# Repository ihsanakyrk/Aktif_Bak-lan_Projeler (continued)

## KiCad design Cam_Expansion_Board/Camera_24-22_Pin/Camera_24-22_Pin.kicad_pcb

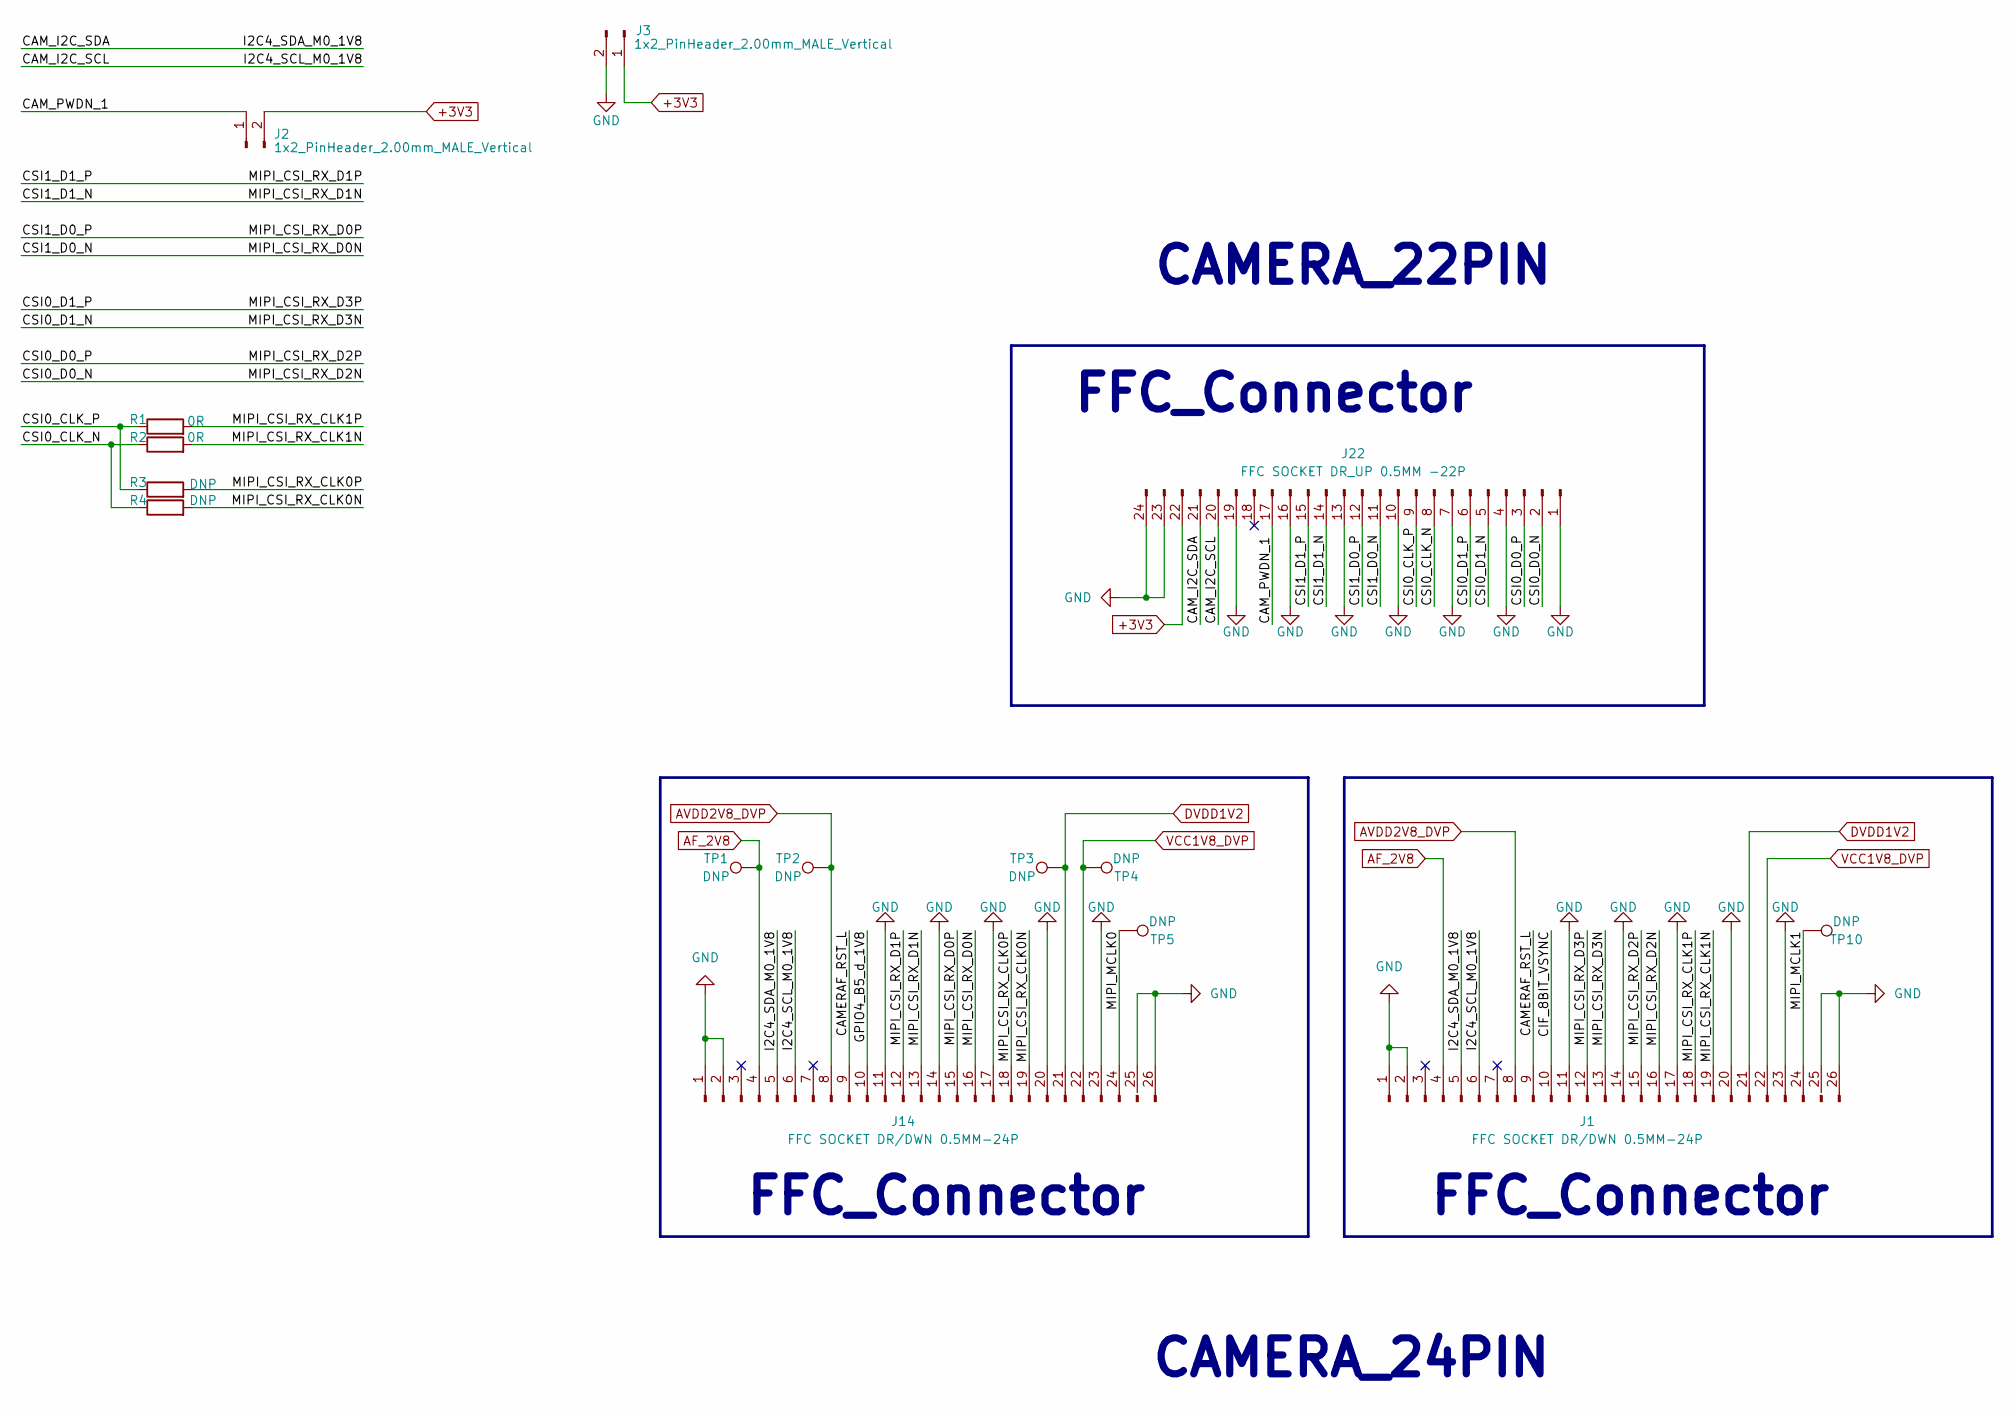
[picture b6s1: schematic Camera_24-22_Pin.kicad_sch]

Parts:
J1, J14: FFC SOCKET DR/DWN 0.5MM-24P; FFC SOCKET DRDWN 0.5MM-24P
J2, J3: 1x2_PinHeader_2.00mm_MALE_Vertical; PinHeader_1x02_P2.00mm_Vertical
J22: FFC SOCKET DR_UP 0.5MM -22P; FFC SOCKET DR_DWN 0.5MM -22P
R1, R2: 0R; R_0603_1608Metric
R3, R4: DNP; R_0603_1608Metric
TP1, TP2, TP3, TP4, TP5, TP10: DNP; Test_Point

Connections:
+3V3: J2.2, J3.1, J22.22
/CAMERAF_RST_L: J1.9, J14.9
/CAM_I2C_SCL: J1.6, J14.6, J22.20
/CAM_I2C_SDA: J1.5, J14.5, J22.21
/CAM_PWDN_1: J2.1, J22.17
/CIF_8BIT_VSYNC: J1.10
/CSI0_CLK_N: J22.8, R2.1, R4.1
/CSI0_CLK_P: J22.9, R1.1, R3.1
/CSI0_D0_N: J1.16, J22.2
/CSI0_D0_P: J1.15, J22.3
/CSI0_D1_N: J1.13, J22.5
/CSI0_D1_P: J1.12, J22.6
/CSI1_D0_N: J14.16, J22.11
/CSI1_D0_P: J14.15, J22.12
/CSI1_D1_N: J14.13, J22.14
/CSI1_D1_P: J14.12, J22.15
/GPIO4_B5_d_1V8: J14.10
/MIPI_CSI_RX_CLK0N: J14.19, R4.2
/MIPI_CSI_RX_CLK0P: J14.18, R3.2
/MIPI_CSI_RX_CLK1N: J1.19, R2.2
/MIPI_CSI_RX_CLK1P: J1.18, R1.2
/MIPI_MCLK0: J14.24, TP5.1
/MIPI_MCLK1: J1.24, TP10.1
AF_2V8: J1.4, J14.4, TP1.1
AVDD2V8_DVP: J1.8, J14.8, TP2.1
DVDD1V2: J1.21, J14.21, TP3.1
GND: J1.1, J1.2, J1.11, J1.14, J1.17, J1.20, J1.23, J1.25 (Pin_23), J1.26 (Pin_24), J3.2, J14.1, J14.2, J14.11, J14.14, J14.17, J14.20, J14.23, J14.25 (Pin_23), J14.26 (Pin_24), J22.1, J22.4, J22.7, J22.10, J22.13, J22.16, J22.19, J22.23, J22.24
VCC1V8_DVP: J1.22, J14.22, TP4.1

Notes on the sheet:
CAMERA_24PIN
FFC_Connector
CAMERA_22PIN

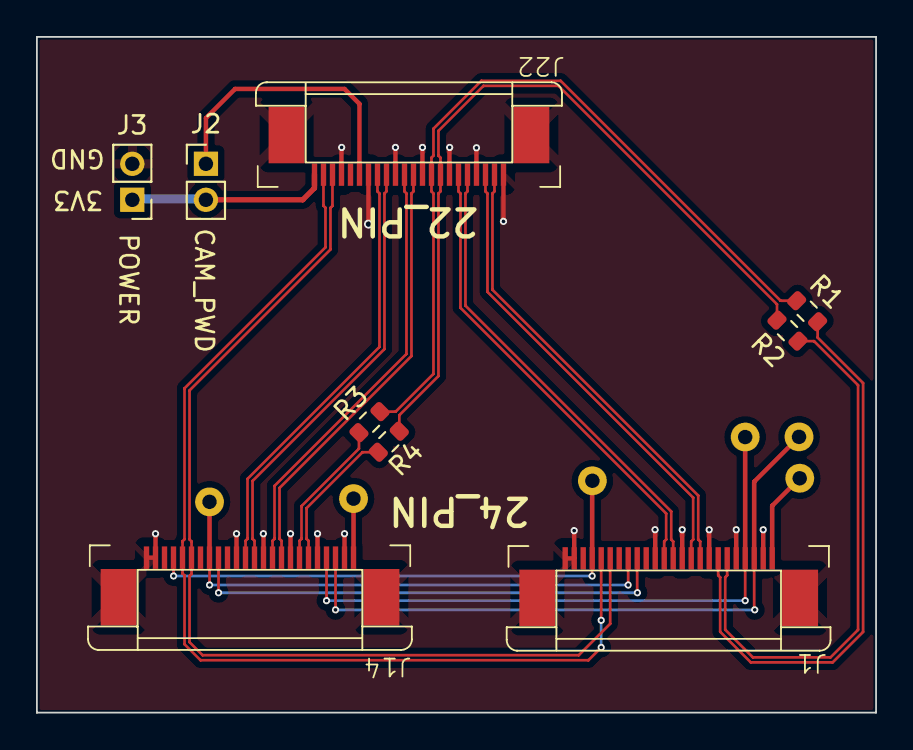
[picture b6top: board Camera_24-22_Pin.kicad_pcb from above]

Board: 2 copper layers, 46.6 x 37.5 mm, 15 parts (0 on the bottom side), 26 nets.

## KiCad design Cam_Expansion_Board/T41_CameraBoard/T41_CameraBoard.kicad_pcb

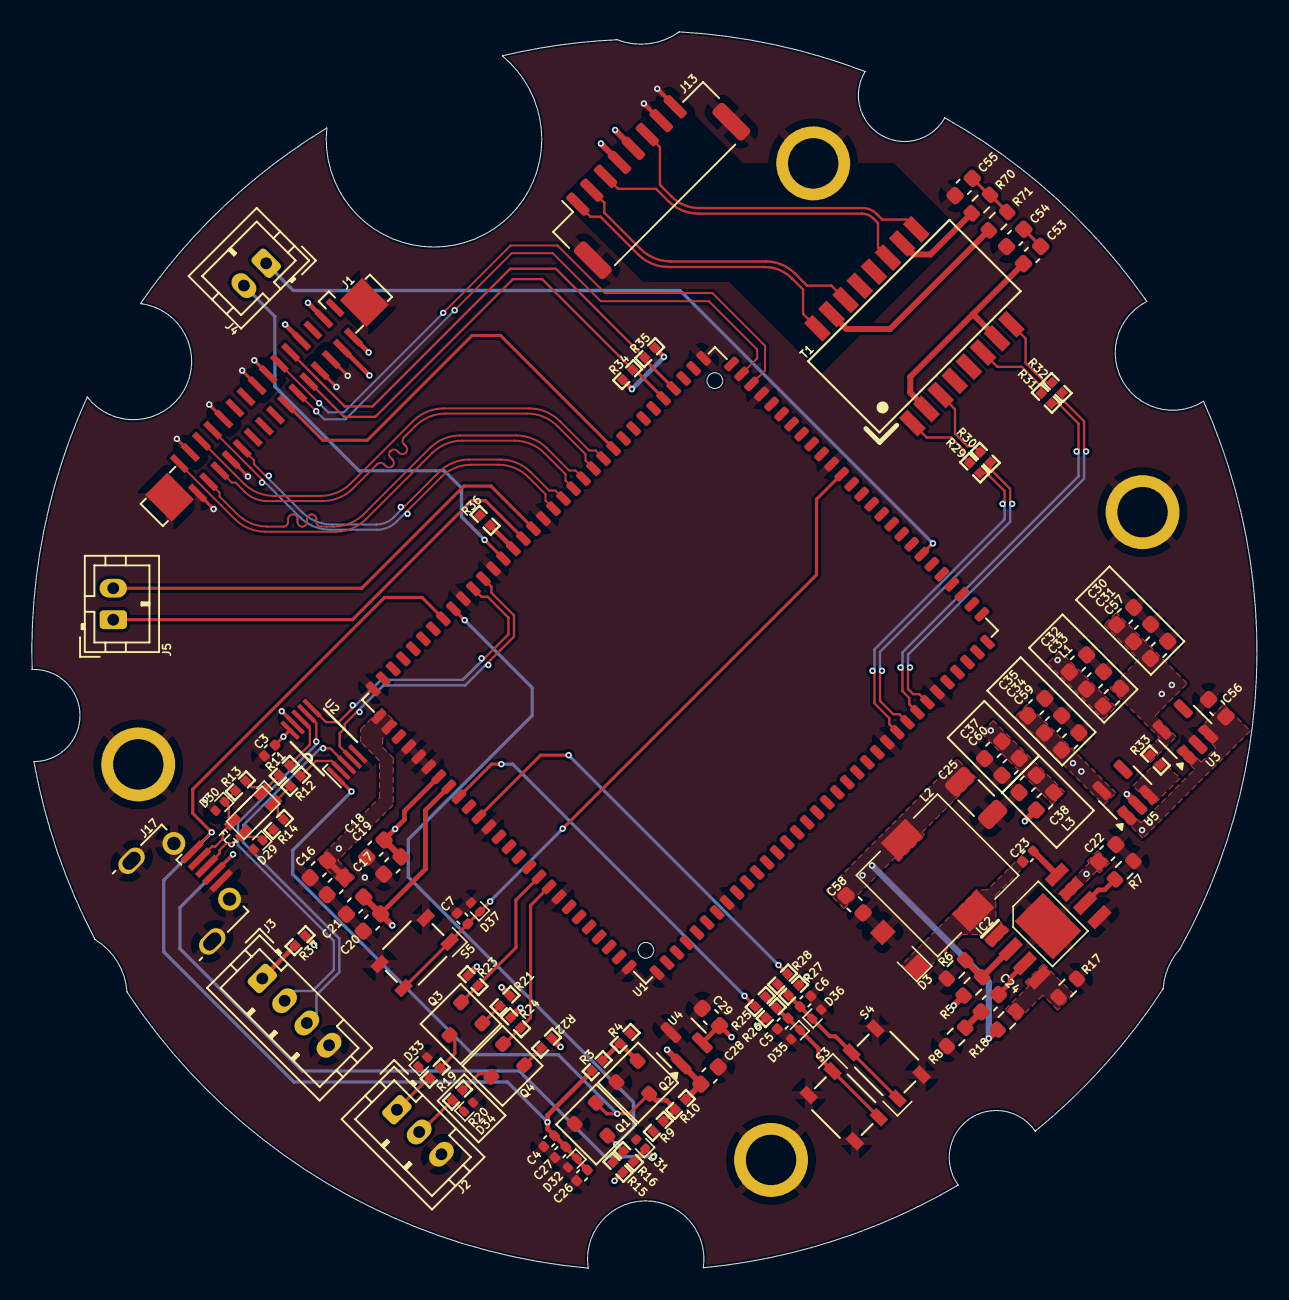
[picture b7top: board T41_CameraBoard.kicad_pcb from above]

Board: 4 copper layers, 77.9 x 78.6 mm, 111 parts (0 on the bottom side), 81 nets.

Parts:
C3, C4, C5, C6, C7, C23: 100nF; C_0402_1005Metric
C16, C18, C20: 10uF/X5R/10V; C_0603_1608Metric
C17, C19, C21: 100nF/X5R/10V; C_0603_1608Metric
C22: 10uF; C_0603_1608Metric
C24: 150pF; C_0603_1608Metric
C25: 22uF/6.3V; C_1206_3216Metric
C26: 10uF/X5R/10V; C_0402_1005Metric
C27: 0.1uF; C_0402_1005Metric
C28, C29, C30, C31, C33, C34, C35, C37, C38: 0.1uF; C_0603_1608Metric
C32: 1uF; C_0603_1608Metric
C53, C54: 0.01uF; C_0603_1608Metric
C55: 1000pF; C_0603_1608Metric
C56, C57, C58, C59, C60: 4.7uF; C_0603_1608Metric
D3: SS34C-MD; SS34FA
D29, D30: ESD5341N
D31, D32, D33, D34, D35, D36, D37: ESD5451N; ESD5341N
FL3: DNP; DLW31SH222SQ2L
H1, H2, H3, H4: DNP; T41_Mounting_Hole
IC2: MP1584EN-LF-Z; MP1584N
J1: AFC11-S30ICA-00
J2: DNP; JST_PH_B3B-PH-K_1x03_P2.00mm_Vertical
J3: DNP; JST_PH_B4B-PH-K_1x04_P2.00mm_Vertical
J4, J5: DNP; JST_PH_B2B-PH-K_1x02_P2.00mm_Vertical
J13: JST_1x8-1MP_P1.25mm_Vertical; JST_1x8_1MP_P1.25mm_Vertical
J17: MICRO XNJ ZB; Micro-B SMD
L1, L3: BLM18PG181SN1; L_0603_1608Metric
L2: SRI0704-100M
Q1, Q2, Q3, Q4: BSS138; SOT-23
R3, R4, R10, R15, R23, R24, R33, R34, R35: 10K; R0402
R5, R7, R8: 100K; R_0603_1608Metric
R6: 24.9K; R_0603_1608Metric
R9, R26, R27: 100K; R0402
R11, R12, R13, R14: 2.2R; R0402
R16, R19, R20: 100R; R0402
R17: 40.2K; R_0603_1608Metric
R18: 210K; R_0603_1608Metric
R21, R22, R25, R28: 1K; R0402
R29, R30, R31, R32, R37: 0R; R0402
R36: DNP; R0402
R70, R71: 75R; R_0603_1608Metric
S3, S4, S5: SKRPANE010
T1: H1102NL
U1: DNP; T41
U2: FSUSB30MUX; SOP50P490X110-10N
U3, U5: rt9013-28gb; SOT-23-5
U4: TLV76033DBZT; SOT-23

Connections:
1V8: C20.2, C21.2, L3.1, R15.2, R26.2, R27.2, R34.1, R35.1, U1.8
3V3: C18.2, C19.2, R23.1, R24.1, U1.7
5V_LAN: C25.1, C56.1, C58.1, L2.2, R18.2, R37.1, U3.1 (IN), U3.3 (EN), U5.1 (IN)
/AGND: R36.1, U1.106
/BOOTSEL0: C7.2 (-), D37.1, S5.1, S5.2, U1.75
/BOOT_MODE: Q1.1 (G), Q2.3 (D), R9.1, R10.1, U2.1 (S)
/HPOUT: J4.2, U1.107
/I2C0_MIPI_DVP_SCK: J1.10, R34.2, U1.91
/I2C0_MIPI_DVP_SDA: J1.9, R35.2, U1.90
/MICNL: J5.1, U1.105
/MICPL: J5.2, U1.104
/MIPI_DVP_PWDN_PA19: J1.12, U1.85
/MIPI_DVP_RESET: J1.11, U1.84
/MIPI_MCLK_PA15/DVP_MCLK_PA15: J1.14, U1.96
/MIPI_RX_2LANE_CLKN0: J1.26, U1.98
/MIPI_RX_2LANE_CLKP0: J1.25, U1.97
/MIPI_RX_2LANE_DN0: J1.29, U1.100
/MIPI_RX_2LANE_DN1: J1.23, U1.102
/MIPI_RX_2LANE_DP0: J1.28, U1.99
/MIPI_RX_2LANE_DP1: J1.22, U1.101
/OTG_ID: D31.1, J17.4 (ID), R16.2
/PPRST_N: R25.2, U1.9
/RX_N1: R32.1, U1.54
/RX_P0+: R31.2, T1.6 (RD+)
/RX_P0-: R32.2, T1.8 (RD-)
/RX_P1: R31.1, U1.53
/SPEAK_EN: J4.1, U1.67
/TX_N0: R30.1, U1.52
/TX_P0: R29.1, U1.51
/TX_P0+: R29.2, T1.1 (TD+)
/TX_P0-: R30.2, T1.3 (TD-)
/UART1-RXD: Q3.3 (D), R19.2
/UART1-TXD: Q4.3 (D), R20.2
/UART1_RXD: Q3.2 (S), R23.2, U1.17
/UART1_TXD: Q4.2 (S), R24.2, U1.18
/USB0ID: Q1.3 (D), R15.1, R16.1, U1.112
/USB-OTG-DN: FL3.1, R11.2, R13.1
/USB-OTG-DP: FL3.4, R12.2, R14.1
/USB_DN: D30.1, FL3.2, J17.2 (DM), R13.2
/USB_DN0: U1.110, U2.6 (D-)
/USB_DP: D29.1, FL3.3, J17.3 (DP), R14.2
/USB_DP0: U1.109, U2.4 (D+)
/USB_HOST_DN: J3.2, U2.7 (HSD2-)
/USB_HOST_DP: J3.3, U2.3 (HSD2+)
/USB_OTG_DN: R11.1, U2.8 (HSD1-)
/USB_OTG_DP: R12.1, U2.2 (HSD1+)
/WKUP: R28.2, U1.11
AF_2V8: C32.2, C33.2, J1.2, L1.2
AVDD2V8_DVP: C30.2, C31.2, C57.1, J1.7, L1.1, R33.2, U3.5 (OUT)
DVDD1V2: C34.2, C35.2, C59.1, J1.3, U5.5 (OUT)
GND: C3.1 (+), C4.1 (+), C5.1 (+), C6.1 (+), C7.1 (+), C16.1, C17.1, C18.1, C19.1, C20.1, C21.1, C22.1, C25.2, C26.1, C27.1, C28.1, C29.1, C30.1, C31.1, C32.1, C33.1, C34.1, C35.1, C37.1, C38.1, C54.2, C55.2, C56.2, C57.2, C58.2, C59.2, C60.2, D3.2, D29.2, D30.2, D31.2, D32.2, D33.2, D34.2, D35.2, D36.2, D37.2, H1.1 (GND), H2.1 (GND), H3.1 (GND), H4.1 (GND), IC2.5 (GND), IC2.9 (EP), J1.6, J1.8, J1.13, J1.15, J1.21, J1.24, J1.27, J1.30, J1.31, J1.32, J2.3, J3.4, J13.7, J13.8, J13.9, J13.10, J17.5 (GND), J17.6 (Shield), Q1.2 (S), Q2.2 (S), R4.1, R6.2, R7.2, R8.2, R9.2, R17.2, R36.2, S3.3, S3.4, S4.3, S4.4, S5.3, S5.4, U1.4, U1.5, U1.6, U1.12, U1.19, U1.26, U1.27, U1.34, U1.50, U1.55, U1.76, U1.83, U1.87, U1.103, U1.108, U1.111, U1.120, U2.5 (GND), U2.9 (/OE), U3.2 (GND), U4.3 (GND), U5.2 (GND)
unnamed: C5.2 (-), D35.1, R25.1, R26.1, S3.1, S3.2
unnamed: C6.2 (-), D36.1, R27.1, R28.1, S4.1, S4.2
unnamed: C24.1, R8.1
unnamed: C53.2, C54.1
unnamed: C55.1, R70.1, R71.1
unnamed: C23.2, IC2.8 (BST)
unnamed: C24.2, IC2.3 (COMP)
unnamed: IC2.2 (EN), R5.2, R6.1
unnamed: IC2.4 (FB), R17.1, R18.1
unnamed: IC2.6 (FREQ), R7.1
unnamed: C23.1, D3.1, IC2.1 (SW), L2.1
unnamed: D33.1, J2.1, R19.1
unnamed: D34.1, J2.2, R20.1
unnamed: J3.1, R37.2
unnamed: Q2.1 (G), R3.1, R4.2
unnamed: Q3.1 (G), R21.2
unnamed: Q4.1 (G), R22.2
unnamed: C53.1, T1.2 (CT1), T1.7 (CT2)
unnamed: R70.2, T1.10 (CT3)
unnamed: R71.2, T1.15 (CT4)
unnamed: R33.1, U5.3 (EN)
RX0_N: J13.6, T1.9 (RX-)
RX0_P: J13.3, T1.11 (RX+)
TRD0_N: J13.2, T1.14 (TX-)
TRD0_P: J13.1, T1.16 (TX+)
USB_VBUS: C4.2 (-), C26.2, C27.2, D32.1, J17.1 (VBUS), R3.2, U1.113
VCC1V8_DVP: C37.2, C38.2, C60.1, J1.4, L3.2
VCC_3V3: C3.2 (-), C28.2, R10.2, U2.10 (VCC), U4.1 (OUT)
VCC_5V: C16.2, C17.2, R21.1, R22.1, U1.1, U1.2
VIN: C22.2, C29.2, IC2.7 (VIN), J13.4, J13.5, R5.1, U4.2 (IN)

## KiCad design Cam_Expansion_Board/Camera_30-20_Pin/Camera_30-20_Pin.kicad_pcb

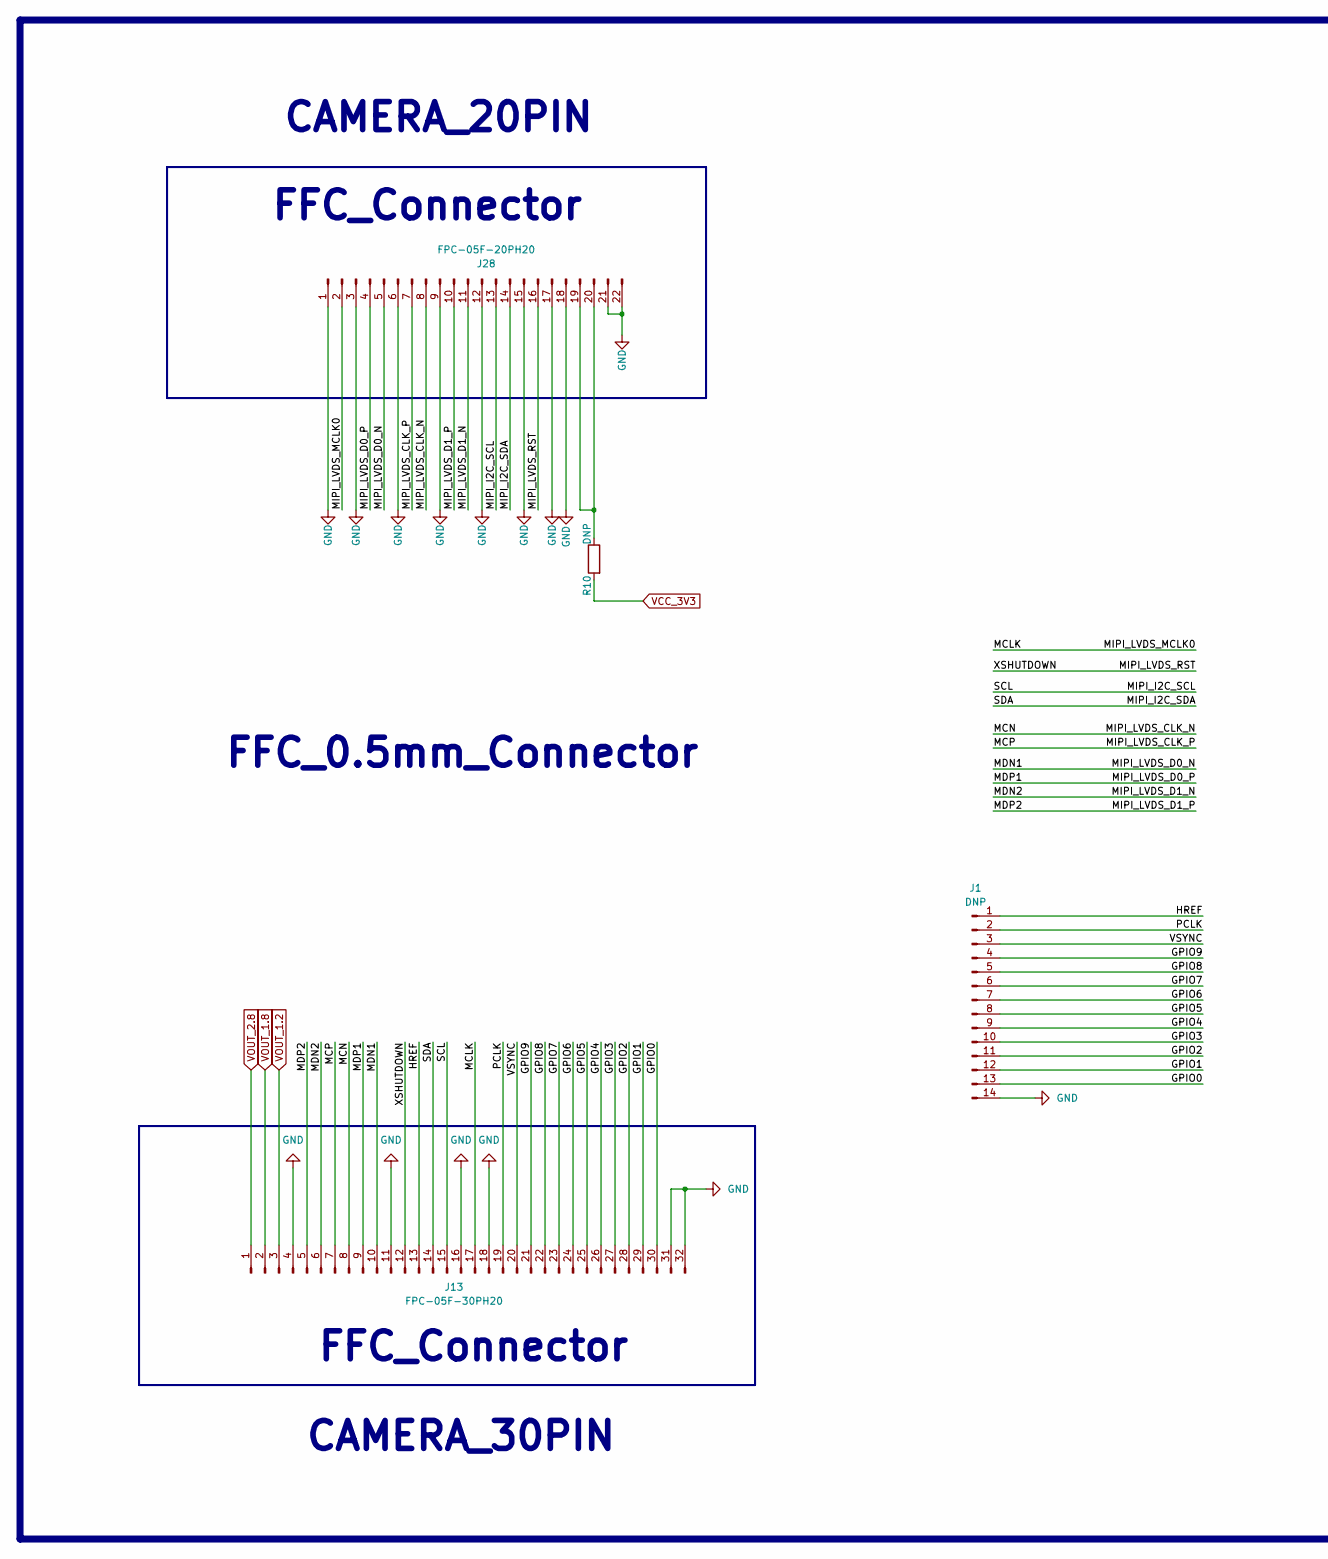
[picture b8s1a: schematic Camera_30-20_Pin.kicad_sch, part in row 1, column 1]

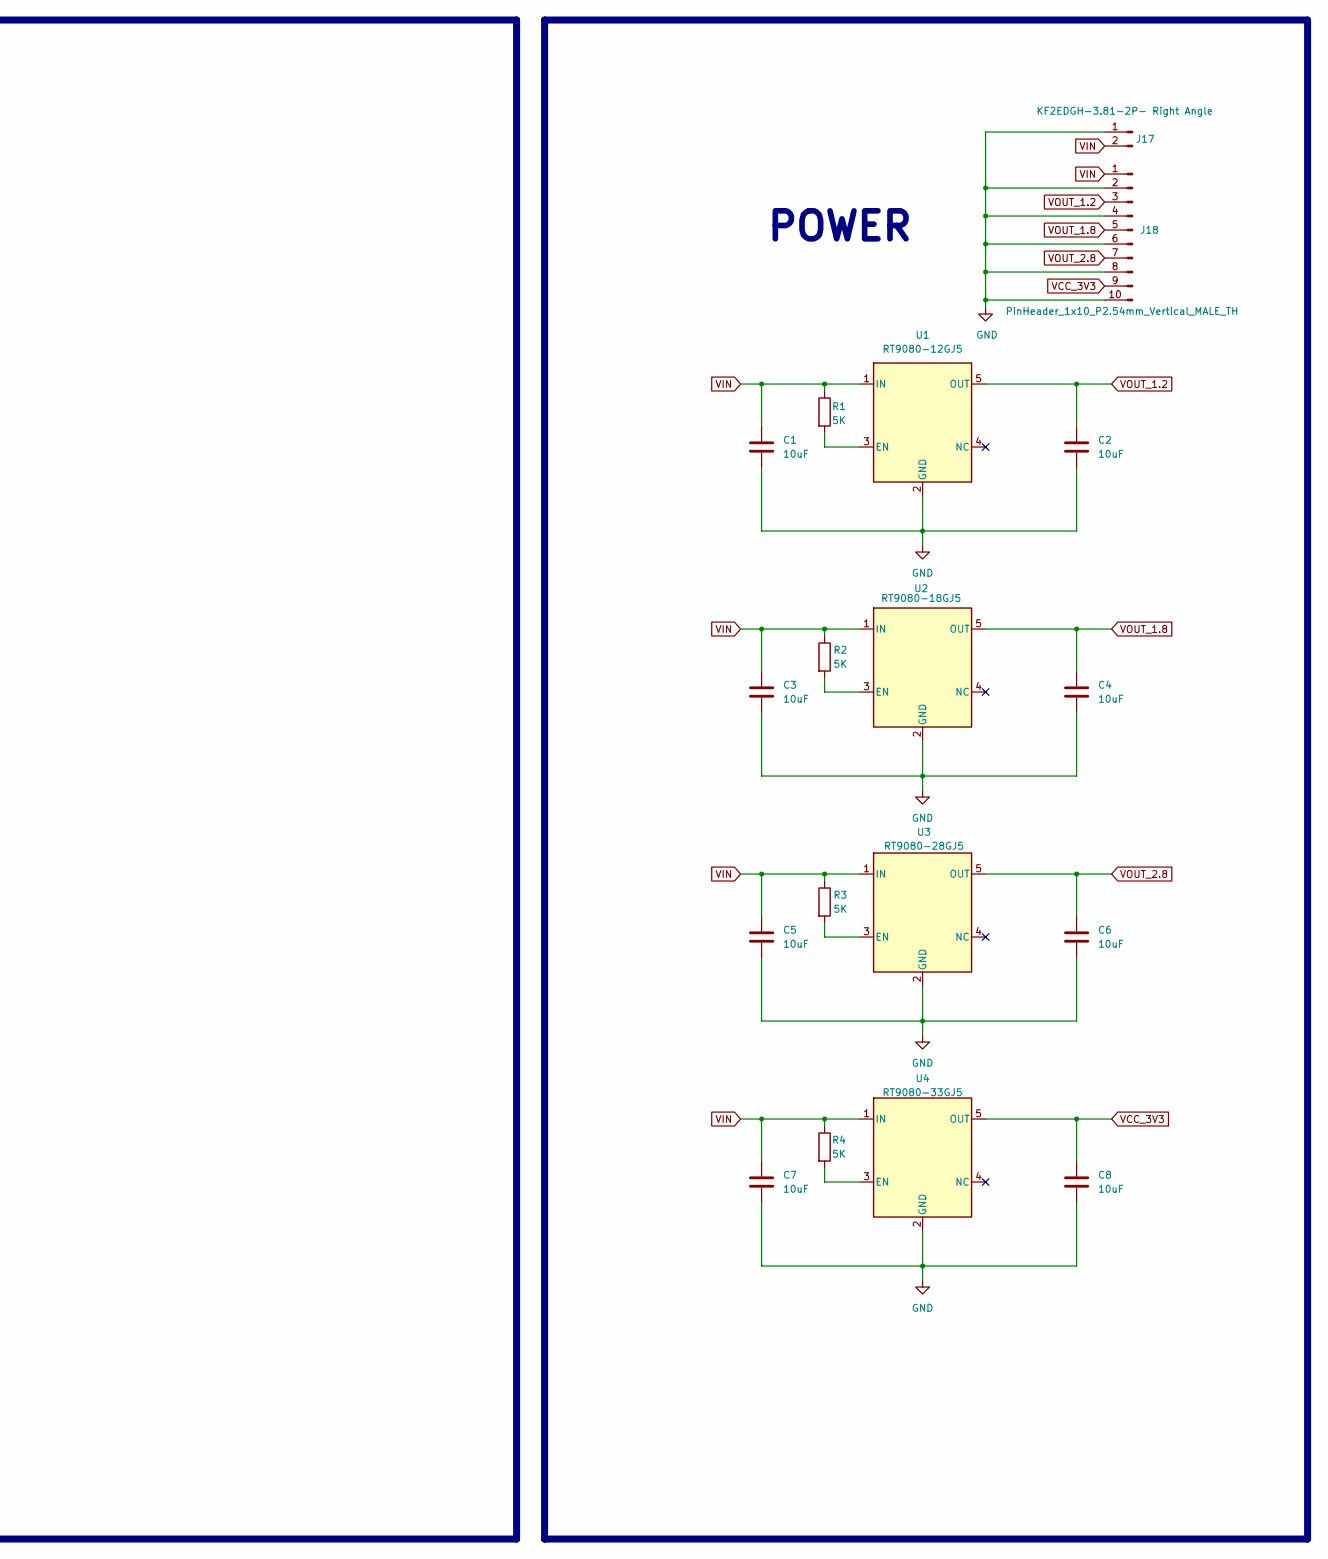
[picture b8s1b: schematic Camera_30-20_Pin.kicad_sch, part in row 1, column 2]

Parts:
C1, C2, C3, C4, C5, C6, C7, C8: 10uF; C_0805_2012Metric
J1: DNP; PinHeader_2x07_P2.00mm_Vertical
J13: FPC-05F-30PH20; FFC SOCKET DR_DWN 0.5MM-30P
J17: KF2EDGH-3.81-2P- Right Angle; KF2EDGH-3.81-2P
J18: PinHeader_1x10_P2.54mm_Vertical_MALE_TH; PinHeader_1x10_P2.54mm_Vertical
J28: FPC-05F-20PH20; FFC SOCKET DR_DWN 0.5MM -20P
R1, R2, R3, R4: 5K; R_0603_1608Metric
R10: DNP; R_0603_1608Metric
U1: RT9080-12GJ5; SOT-23-5
U2: RT9080-18GJ5; SOT-23-5
U3: RT9080-28GJ5; SOT-23-5
U4: RT9080-33GJ5; SOT-23-5

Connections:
/GPIO0: J1.13, J13.30
/GPIO1: J1.12, J13.29
/GPIO2: J1.11, J13.28
/GPIO3: J1.10, J13.27
/GPIO4: J1.9, J13.26
/GPIO5: J1.8, J13.25
/GPIO6: J1.7, J13.24
/GPIO7: J1.6, J13.23
/GPIO8: J1.5, J13.22
/GPIO9: J1.4, J13.21
/HREF: J1.1, J13.13
/MCLK: J13.17, J28.2
/MCN: J13.8, J28.8
/MCP: J13.7, J28.7
/MDN1: J13.10, J28.5
/MDN2: J13.6, J28.11
/MDP1: J13.9, J28.4
/MDP2: J13.5, J28.10
/MIPI_I2C_SCL: J13.15, J28.13
/MIPI_I2C_SDA: J13.14, J28.14
/MIPI_LVDS_RST: J13.12, J28.16
/PCLK: J1.2, J13.19
/VSYNC: J1.3, J13.20
GND: C1.2, C2.2, C3.2, C4.2, C5.2, C6.2, C7.2, C8.2, J1.14 (Pin_13), J13.4, J13.11, J13.16, J13.18, J13.31 (Pin_29), J13.32 (Pin_30), J17.1, J18.2, J18.4, J18.6, J18.8, J18.10, J28.1, J28.3, J28.6, J28.9, J28.12, J28.15, J28.17, J28.18, J28.21, J28.22, U1.2 (GND), U2.2 (GND), U3.2 (GND), U4.2 (GND)
unnamed: J28.19, J28.20, R10.1
unnamed: R1.2, U1.3 (EN)
unnamed: R2.2, U2.3 (EN)
unnamed: R3.2, U3.3 (EN)
unnamed: R4.2, U4.3 (EN)
VCC_3V3: C8.1, J18.9, R10.2, U4.5 (OUT)
VIN: C1.1, C3.1, C5.1, C7.1, J17.2, J18.1, R1.1, R2.1, R3.1, R4.1, U1.1 (IN), U2.1 (IN), U3.1 (IN), U4.1 (IN)
VOUT_1.2: C2.1, J13.3, J18.3, U1.5 (OUT)
VOUT_1.8: C4.1, J13.2, J18.5, U2.5 (OUT)
VOUT_2.8: C6.1, J13.1, J18.7, U3.5 (OUT)

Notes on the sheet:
CAMERA_20PIN
CAMERA_30PIN
FFC_0.5mm_Connector
FFC_Connector
POWER

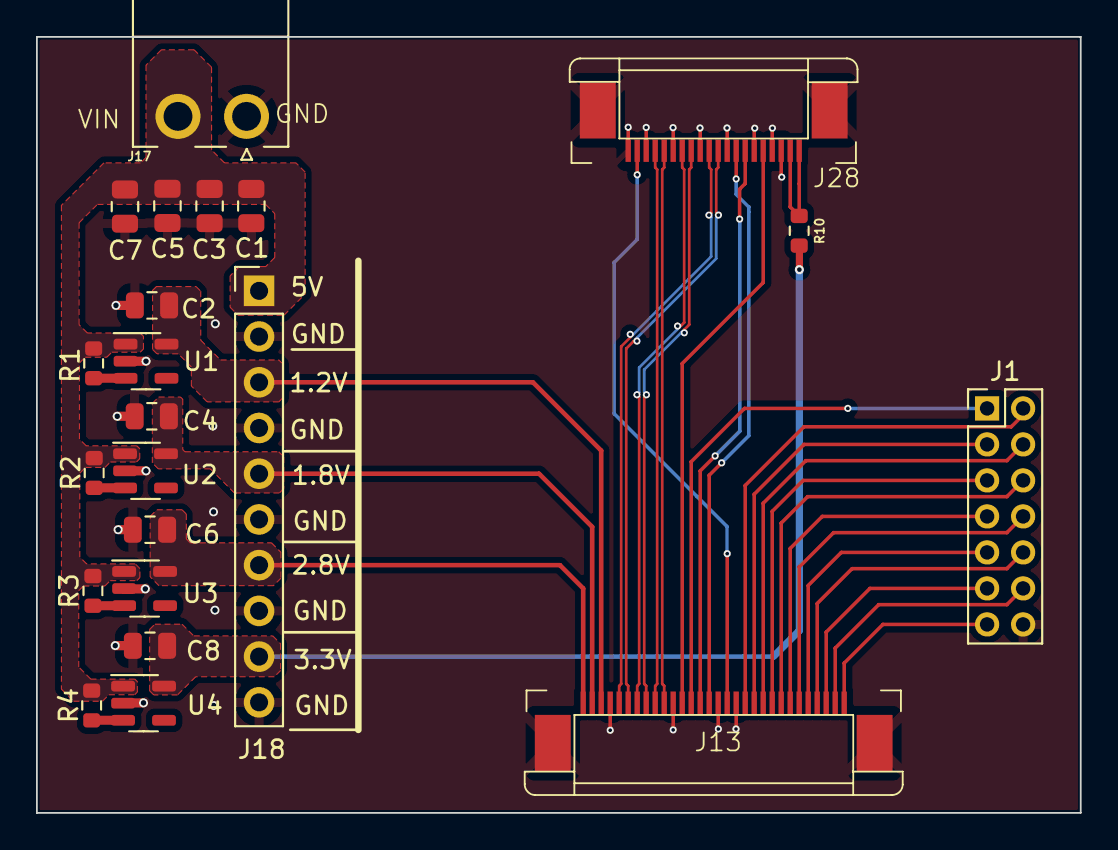
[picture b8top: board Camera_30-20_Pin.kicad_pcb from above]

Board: 2 copper layers, 58.0 x 43.1 mm, 22 parts (0 on the bottom side), 34 nets.

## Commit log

2025-08-28 ilk commit
2025-08-29 camera expansion board yapılacak
